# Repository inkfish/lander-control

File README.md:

# Lander Control Board for the Inkfish Hadal Exploration System

This repository contains firmware source code and hardware design files for the Lander Control Board used by the Inkfish Hadal Exploration System.

The Lander Control Board is responsible for switching power to the lander's peripherals, including a CTD, acoustic modem, camera, and lights. The board logs CTD data and responds to commands received via the acoustic modem.

The Lander Control Board is a motherboard for a [Raspberry Pi Pico][Pico]. A secondary microcontroller, an [Espressif ESP32-C6-WROOM-1U][ESP32], adds Wi-Fi capabilities. Timekeeping is assisted by an external GPS receiver along with an [Adafruit DS3231 Precision Real-Time Clock Breakout][RTC].

The firmware is written in [CircuitPython][] in order to be easily modifiable in the field and for compatibility with future microcontrollers. Data will be logged in the [MCAP][] file format.

[CircuitPython]: https://circuitpython.org/
[ESP32]: https://www.espressif.com/en/products/socs/esp32-c6
[MCAP]: https://mcap.dev/
[Pico]: https://www.raspberrypi.com/products/raspberry-pi-pico/
[RTC]: https://www.adafruit.com/product/3013

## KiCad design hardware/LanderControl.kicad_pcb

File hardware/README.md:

# Hardware Design for Lander Control Board

This directory contains [KiCad][] schematic and PCB files for the Lander Control Board.

Designed by [Boston Precision Motion][] for Inkfish.

[Boston Precision Motion]: https://bostonprecisionmotion.com/
[KiCad]: https://www.kicad.org

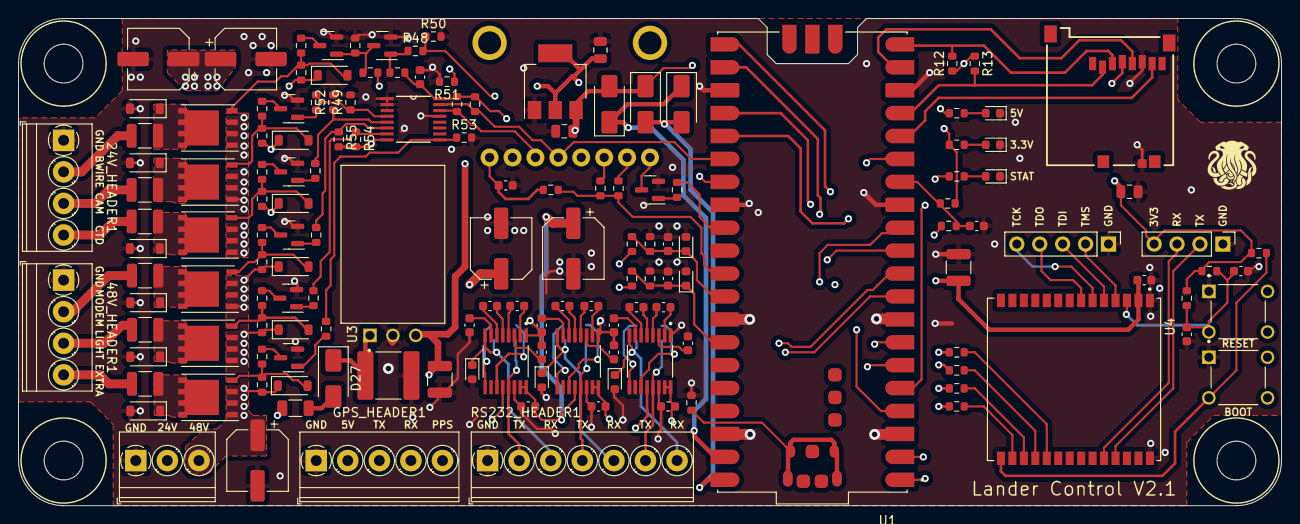
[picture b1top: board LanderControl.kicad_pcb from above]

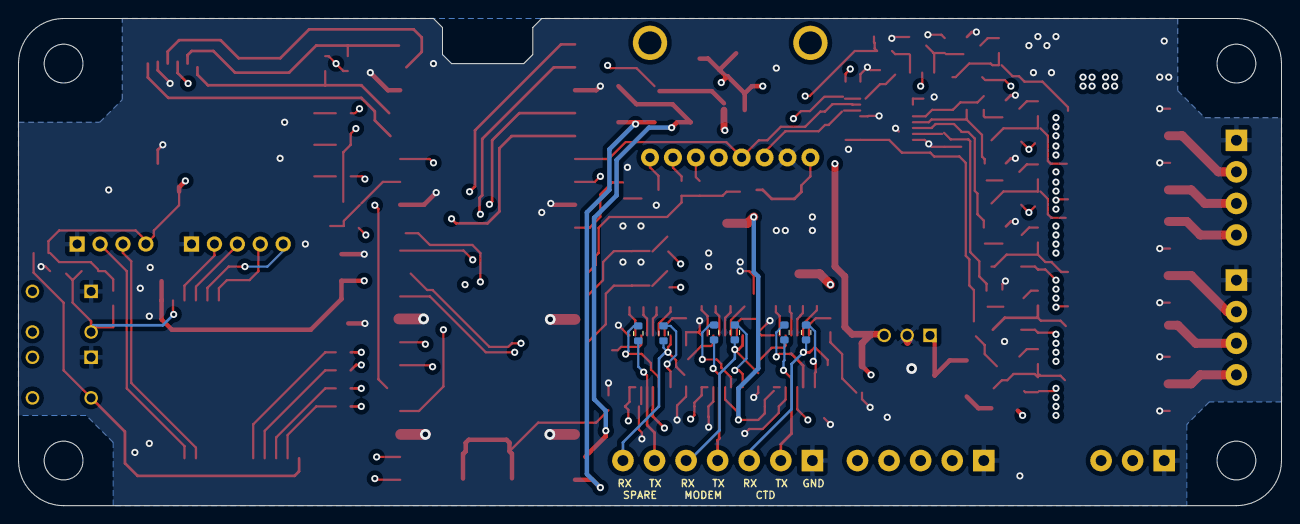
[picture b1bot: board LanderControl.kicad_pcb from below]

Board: 4 copper layers, 140.0 x 54.0 mm, 157 parts (6 on the bottom side), 115 nets.

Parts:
24V_HEADER1, 48V_HEADER1: Conn_01x04; TerminalBlock_Phoenix_PT-1,5-4-3.5-H_1x04_P3.50mm_Horizontal
C1, C2, C30: 1nF; C_0603_1608Metric
C3, C5, C12, C13, C14, C15, C16, C17, C18, C19, C20, C21, C22, C23, C24, C25, C26: 100nF; C_0603_1608Metric
C4, C11, C27: 1uF; C_0603_1608Metric
C6, C8: 22uF; C_1210_3225Metric
C7: 10uF; C_2220_5650Metric
C9, C10: 1uF; C_0805_2012Metric
C28, C29, C35, C37: >25V>25uF; CP_Elec_6.3x4.9
C31: 4.7uF; C_0805_2012Metric
C36: >50V>25uF; CP_Elec_6.3x4.9
D1, D2, D8, D10, D12: D_Zener; D_0603_1608Metric
D3, D25, D26, D27: B120-E3; D_SMA
D4, D5, D6: LED; D_0603_1608Metric
D13, D14, D17, D18, D21, D22: D_Zener; D_SOD-123
D15, D16, D19, D23, D24: 1N4148W; D_SOD-123
D20: SS210LW; D_SOD-123
DNP1, DNP2, DNP3, DNP4, DNP5, DNP6: 0; R_0603_1608Metric
DNP_R1: 0; R_0603_1608Metric
GPS_HEADER1: Conn_01x05; TerminalBlock_Phoenix_PT-1,5-5-3.5-H_1x05_P3.50mm_Horizontal
J2: Conn_01x04; PinHeader_1x04_P2.54mm_Vertical
J3: Conn_01x05; PinHeader_1x05_P2.54mm_Vertical
J5: MEM2051-00-195-00-A; GCT_MEM2051-00-195-00-A
PWR_IN1: Conn_01x03; TerminalBlock_Phoenix_PT-1,5-3-3.5-H_1x03_P3.50mm_Horizontal
Q1, Q2, Q3, Q4, Q5, Q6, Q7, Q8: BC846; SOT-23
R1: 49.9k; R_0603_1608Metric
R2, R4: 4.99k; R_0603_1608Metric
R3, R34: 100k; R_0603_1608Metric
R5, R6, R7, R21, R48: 560; R_0603_1608Metric
R8, R9, R12, R13, R14, R20, R25, R26, R27, R28, R29, R30, R31, R32, R35, R36, R37, R38, R39, R40, R41, R42, R43, R44, R45, R46: 10k; R_0603_1608Metric
R10, R11, R15, R16, R22, R23, R24: 0; R_0603_1608Metric
R19: 2.2; R_1206_3216Metric
R33: 4.7k; R_0603_1608Metric
R47: 47; R_0603_1608Metric
R49, R50, R51, R52, R53, R54, R55: 1k; R_0603_1608Metric
RS232_HEADER1: Conn_01x07; TerminalBlock_Phoenix_PT-1,5-7-3.5-H_1x07_P3.50mm_Horizontal
S1, S2: TS02-66-100-BK-100-LCR-D; SW_TS02-66-100-BK-100-LCR-D
TH1, TH2, TH3, TH4, TH5, TH6: Thermistor_PTC; R_1210_3225Metric
U1: SC0915; MODULE_SC0915
U3: P7805-500R; CONV_P7805-500R
U4: ESP32-C6-WROOM-1U-N4; XCVR_ESP32-C6-WROOM-1U-N4
U5: DS3231_breakout
U6, U7, U8: SN65C3221EPWR; SOP65P640X120-16N
U9, U10, U11, U12, U13, U14: SI7489DP-T1-E3; PowerPAK_SO-8_Single
U15: TCA9534APWR; SOP65P640X110-16N
U16: AMS1117; SOT-223-3_TabPin2

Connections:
+3V3: C5.2, C6.2, C10.1, C11.1, C16.2, C21.2, C26.2, C27.1, C28.1, C31.1, J2.4, J5.4 (VDD), R6.1, R8.2, R9.2, R12.1, R13.1, R14.1, R20.1, R24.2, R31.2, R45.1, R46.1, U4.2 (3V3), U5.1 (3V3), U6.12 (FORCEON), U6.15 (VCC), U6.16 (~FORCEOFF), U7.12 (FORCEON), U7.15 (VCC), U7.16 (~FORCEOFF), U8.12 (FORCEON), U8.15 (VCC), U8.16 (~FORCEOFF), U15.16 (VDD), U16.2 (VO)
+5V: C8.2, C9.1, D3.2 (A), D25.1 (K), GPS_HEADER1.2, R5.1, U3.3 (+VO), U16.3 (VI)
+24V: C35.1, C37.1, D14.1 (K), D18.1 (K), D22.1 (K), PWR_IN1.2, R1.1, R19.2, R29.2, R37.2, R43.2, U10.1 (S), U10.2 (S), U10.3 (S), U12.1 (S), U12.2 (S), U12.3 (S), U14.1 (S), U14.2 (S), U14.3 (S)
+48V: C36.1, D13.1 (K), D17.1 (K), D21.1 (K), PWR_IN1.3, R3.1, R27.2, R35.2, R41.2, U9.1 (S), U9.2 (S), U9.3 (S), U11.1 (S), U11.2 (S), U11.3 (S), U13.1 (S), U13.2 (S), U13.3 (S)
/CAMERA_POWER: R26.2, R49.1, U15.4 (IO0)
/CTD_POWER: R40.2, R52.1, U15.5 (IO1)
/ESP32/BOOT: R46.2, S2.3, U4.15 (IO9)
/ESP32/EN: C3.1, C4.2, R14.2, R45.2, S1.3, U4.3 (EN)
/ESP32/ESP_RX: J2.3, U4.24 (RXD0/GPIO17)
/ESP32/ESP_TX: J2.2, U4.25 (TXD0/GPIO16)
/ESP32/TCK: J3.5, U4.6 (IO6)
/ESP32/TDI: J3.3, U4.5 (IO5)
/ESP32/TDO: J3.4, U4.7 (IO7)
/ESP32/TMS: J3.2, U4.4 (IO4)
/LIGHT_POWER: R32.2, R54.1, U15.7 (IO3)
/MODEM_POWER: R25.2, R55.1, U15.6 (IO2)
/SPARE_48V_POWER: R39.2, R53.1, U15.9 (IO4)
/connectors/CTD_RX_232: D8.1 (K), DNP2.1, RS232_HEADER1.3, U6.8 (RIN)
/connectors/CTD_TX_232: DNP1.2, RS232_HEADER1.2, U6.13 (DOUT)
/connectors/MODEM_RX_232: D10.1 (K), DNP4.1, RS232_HEADER1.5, U7.8 (RIN)
/connectors/MODEM_TX_232: DNP3.2, RS232_HEADER1.4, U7.13 (DOUT)
/connectors/SPARE_RX_232: D12.1 (K), DNP6.1, RS232_HEADER1.7, U8.8 (RIN)
/connectors/SPARE_TX_232: DNP5.2, RS232_HEADER1.6, U8.13 (DOUT)
BURN_WIRE_PWR_OUT: 24V_HEADER1.2, TH4.1
CAMERA_PWR_OUT: 24V_HEADER1.3, TH2.1
EXTRA_24V_PWR_OUT: 24V_HEADER1.4, TH6.1
EXTRA_48V_PWR_OUT: 48V_HEADER1.4, TH5.1
GND: 24V_HEADER1.1, 48V_HEADER1.1, C1.2, C2.2, C3.2, C4.1, C5.1, C6.1, C7.2, C8.1, C9.2, C10.2, C11.2, C14.1, C15.1, C16.1, C19.1, C20.1, C21.1, C24.1, C25.1, C26.1, C27.2, C28.2, C29.2, C30.2, C31.2, C35.2, C36.2, C37.2, D1.2 (A), D2.2 (A), D4.1 (K), D5.1 (K), D6.1 (K), D8.2 (A), D10.2 (A), D12.2 (A), D15.2 (A), D16.2 (A), D19.2 (A), D20.2 (A), D23.2 (A), D24.2 (A), DNP_R1.2, GPS_HEADER1.1, J2.1, J3.1, J5.6 (VSS), J5.9 (DETECH), PWR_IN1.1, Q1.2 (E), Q2.2 (E), Q3.2 (E), Q4.2 (E), Q5.2 (E), Q6.2 (E), Q7.2 (E), Q8.2 (E), R2.2, R4.2, R34.2, R49.2, R50.2, R51.2, R52.2, R53.2, R54.2, R55.2, RS232_HEADER1.1, S1.1, S2.1, U1.3 (GND), U1.8 (GND), U1.13 (GND), U1.18 (GND), U1.23 (GND), U1.28 (GND), U1.33 (AGND), U1.38 (GND), U1.D2 (GND), U3.2 (GND), U4.1 (GND), U4.28 (GND__1), U5.2 (GND), U6.1 (~EN), U6.14 (GND), U7.1 (~EN), U7.14 (GND), U8.1 (~EN), U8.14 (GND), U15.1 (A0), U15.2 (A1), U15.3 (A2), U15.8 (VSS), U15.13 (~WC), U16.1 (ADJ)
GP0: DNP1.1, U1.1 (GP0), U6.11 (DIN)
GP1: DNP2.2, U1.2 (GP1), U6.9 (ROUT)
GP2: R48.2, R50.1, U1.4 (GP2)
GP3: R7.1, U1.5 (GP3)
GP4: DNP3.1, U1.6 (GP4), U7.11 (DIN)
GP5: DNP4.2, U1.7 (GP5), U7.9 (ROUT)
GP6: DNP5.1, U1.9 (GP6), U8.11 (DIN)
GP7: DNP6.2, U1.10 (GP7), U8.9 (ROUT)
GP8: GPS_HEADER1.3, U1.11 (GP8)
GP9: GPS_HEADER1.4, U1.12 (GP9)
GP10: C30.1, R24.1, R47.2, U1.14 (GP10)
GP11: R33.2, R51.1, U1.15 (GP11)
GP12: J5.7 (DATA0), U1.16 (GP12)
GP13: J5.2 (DATA3/CD), R13.2, U1.17 (GP13)
GP14: J5.5 (CLK), U1.19 (GP14)
GP15: J5.3 (CMD), R12.2, U1.20 (GP15)
GP16: R10.1, U1.21 (GP16)
GP17: R11.1, U1.22 (GP17)
GP18: R16.1, U1.24 (GP18)
GP19: R15.1, U1.25 (GP19)
GP20: R8.1, U1.26 (GP20), U5.4 (SDA), U15.15 (SDA)
GP21: R9.1, U1.27 (GP21), U5.3 (SCL), U15.14 (SCL)
GP22: R21.1, U1.29 (GP22)
GP26: R20.2, R22.1, R23.1, U1.31 (GP26)
GP27: C1.1, D1.1 (K), R1.2, R2.1, U1.32 (GP27)
GP28: C2.1, D2.1 (K), R3.2, R4.1, U1.34 (GP28)
LIGHT_PWR_OUT: 48V_HEADER1.3, TH3.1
MODEM_PWR_OUT: 48V_HEADER1.2, TH1.1
unnamed: D4.2 (A), R5.2
unnamed: D5.2 (A), R6.2
unnamed: D6.2 (A), R7.2
unnamed: D13.2 (A), R27.1, R28.2, U9.4 (G)
unnamed: D14.2 (A), R29.1, R30.2, U10.4 (G)
unnamed: D15.1 (K), TH1.2, U9.5 (D)
unnamed: D16.1 (K), TH2.2, U10.5 (D)
unnamed: D17.2 (A), R35.1, R36.2, U11.4 (G)
unnamed: D18.2 (A), R37.1, R38.2, U12.4 (G)
unnamed: D19.1 (K), TH3.2, U11.5 (D)
unnamed: D20.1 (K), TH4.2, U12.5 (D)
unnamed: D21.2 (A), R41.1, R42.2, U13.4 (G)
unnamed: D22.2 (A), R43.1, R44.2, U14.4 (G)
unnamed: D23.1 (K), TH5.2, U13.5 (D)
unnamed: D24.1 (K), TH6.2, U14.5 (D)
unnamed: D3.1 (K), D26.1 (K), U1.39 (VSYS)
unnamed: D27.2 (A), R19.1
unnamed: C7.1, C29.1, D27.1 (K), U3.1 (+VIN)
unnamed: DNP_R1.1, U1.A (USB_SHIELD), U1.B (USB_SHIELD), U1.C (USB_SHIELD), U1.D (USB_SHIELD)
unnamed: GPS_HEADER1.5, R47.1
unnamed: Q1.1 (B), R21.2
unnamed: Q1.3 (C), U5.8 (!RTC_RST)
unnamed: Q2.1 (B), R25.1
unnamed: Q2.3 (C), R28.1
unnamed: Q3.1 (B), R26.1
unnamed: Q3.3 (C), R30.1
unnamed: Q4.1 (B), R31.1, R48.1
unnamed: Q4.3 (C), Q6.1 (B), R33.1, R34.1
unnamed: Q5.1 (B), R32.1
unnamed: Q5.3 (C), R36.1
unnamed: Q6.3 (C), R38.1
unnamed: Q7.1 (B), R39.1
unnamed: Q7.3 (C), R42.1
unnamed: Q8.1 (B), R40.1
unnamed: Q8.3 (C), R44.1
unnamed: R11.2, U4.16 (IO18)
unnamed: R16.2, U4.17 (IO19)
unnamed: R10.2, U4.18 (IO20)
unnamed: R15.2, U4.19 (IO21)
unnamed: R23.2, U5.6 (32KHZ)
unnamed: R22.2, U5.7 (SQW)
unnamed: C12.1, U6.2 (C1+)
unnamed: C12.2, U6.4 (C1-)
unnamed: C13.1, U6.5 (C2+)
unnamed: C13.2, U6.6 (C2-)
unnamed: C15.2, U6.3 (V+)
unnamed: C14.2, U6.7 (V-)
unnamed: C17.1, U7.2 (C1+)
unnamed: C17.2, U7.4 (C1-)
unnamed: C18.1, U7.5 (C2+)
unnamed: C18.2, U7.6 (C2-)
unnamed: C20.2, U7.3 (V+)
unnamed: C19.2, U7.7 (V-)
unnamed: C22.1, U8.2 (C1+)
unnamed: C22.2, U8.4 (C1-)
unnamed: C23.1, U8.5 (C2+)
unnamed: C23.2, U8.6 (C2-)
unnamed: C25.2, U8.3 (V+)
unnamed: C24.2, U8.7 (V-)

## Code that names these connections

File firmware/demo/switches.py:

'''

'''

import board
import busio
import digitalio

import adafruit_pcf8574


gpio_expander = adafruit_pcf8574.PCF8574(
    busio.I2C(
        board.GP21,  # SCL
        board.GP20   # SDA
    )
)


# Power switches attached to the GPIO expander
pin_camera_power = gpio_expander.get_pin(0)
pin_spare_24v_power = gpio_expander.get_pin(1)
pin_modem_power = gpio_expander.get_pin(2)
pin_light_power = gpio_expander.get_pin(3)
pin_spare_48v_power = gpio_expander.get_pin(4)
pin_burn_wire = gpio_expander.get_pin(6)

for pin in [ pin_camera_power, pin_spare_24v_power, pin_modem_power,
             pin_light_power, pin_spare_48v_power, pin_burn_wire ]:
    pin.switch_to_output()


# Enable pin for burn wire
pin_burn_enable = digitalio.DigitalInOut(board.GP2)
pin_burn_enable.switch_to_output()


# Menu
print('''
Enter command: [number] [on|off]
    (24V)  1: Camera   2: Burn wire   3: Spare
    (48V)  4: Modem    5: Lights      6: Spare
           7: Burn wire enable
''')

while True:
    choice, _, state = input('> ').partition(' ')

    if state.lower() not in ('on', 'off', '1', '0', 'hi', 'high', 'lo', 'low'):
        print(f'Unknown state {state}, try again.')
        continue

    state = state.lower() in ('on', '1', 'hi', 'high')

    try:
        {
            '1': pin_camera_power,
            '2': pin_burn_wire,
            '3': pin_spare_24v_power,
            '4': pin_modem_power,
            '5': pin_light_power,
            '6': pin_spare_48v_power,
            '7': pin_burn_enable
        }[choice].value = state
    except KeyError:
        print(f'Unknown pin {choice}, try again.')
        continue

    print('Switched pin', choice, 'to', 'on' if state else 'off')

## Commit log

2023-10-14 Add CircuitPython demos
2023-10-14 Add means of mocking CircuitPython APIs on CPython
2023-10-14 Add an example of a mock analog GPIO pin
2023-10-27 Add demo for LED control. Closes #14.
2024-01-23 Change resistor values to match schematic
2024-01-31 Add workaround script for macOS
2024-01-31 Update demo script for switches
2024-02-24 Move firmware code to subdirectory
2024-02-24 Exclude Adafruit DS3231 breakout from JLCPCB BOM
2024-02-24 Clean up silkscreen labels
2024-02-24 Replace PCA9500 I/O expander with TCA9534
2024-02-24 Add LCSC IDs for terminal blocks
2024-02-24 Remove diodes from voltage monitoring circuit
2024-02-24 Initial import
2024-02-24 Clean up tracks and vias, refill zones
2024-02-24 Add missing library placeholders
2024-02-24 Add Inkfish logo to silkscreen
2024-02-24 Update references from ESP32-S2 to ESP32-C6
2024-02-24 Add JLCPCB part and rotation mapping info
2024-02-24 Add READMEs for the hardware design
2024-02-24 Add missing 3D models
2024-02-25 Add repository README
2024-02-26 Remove unneeded ESP32 thermal pads
2024-02-26 Refill zones
